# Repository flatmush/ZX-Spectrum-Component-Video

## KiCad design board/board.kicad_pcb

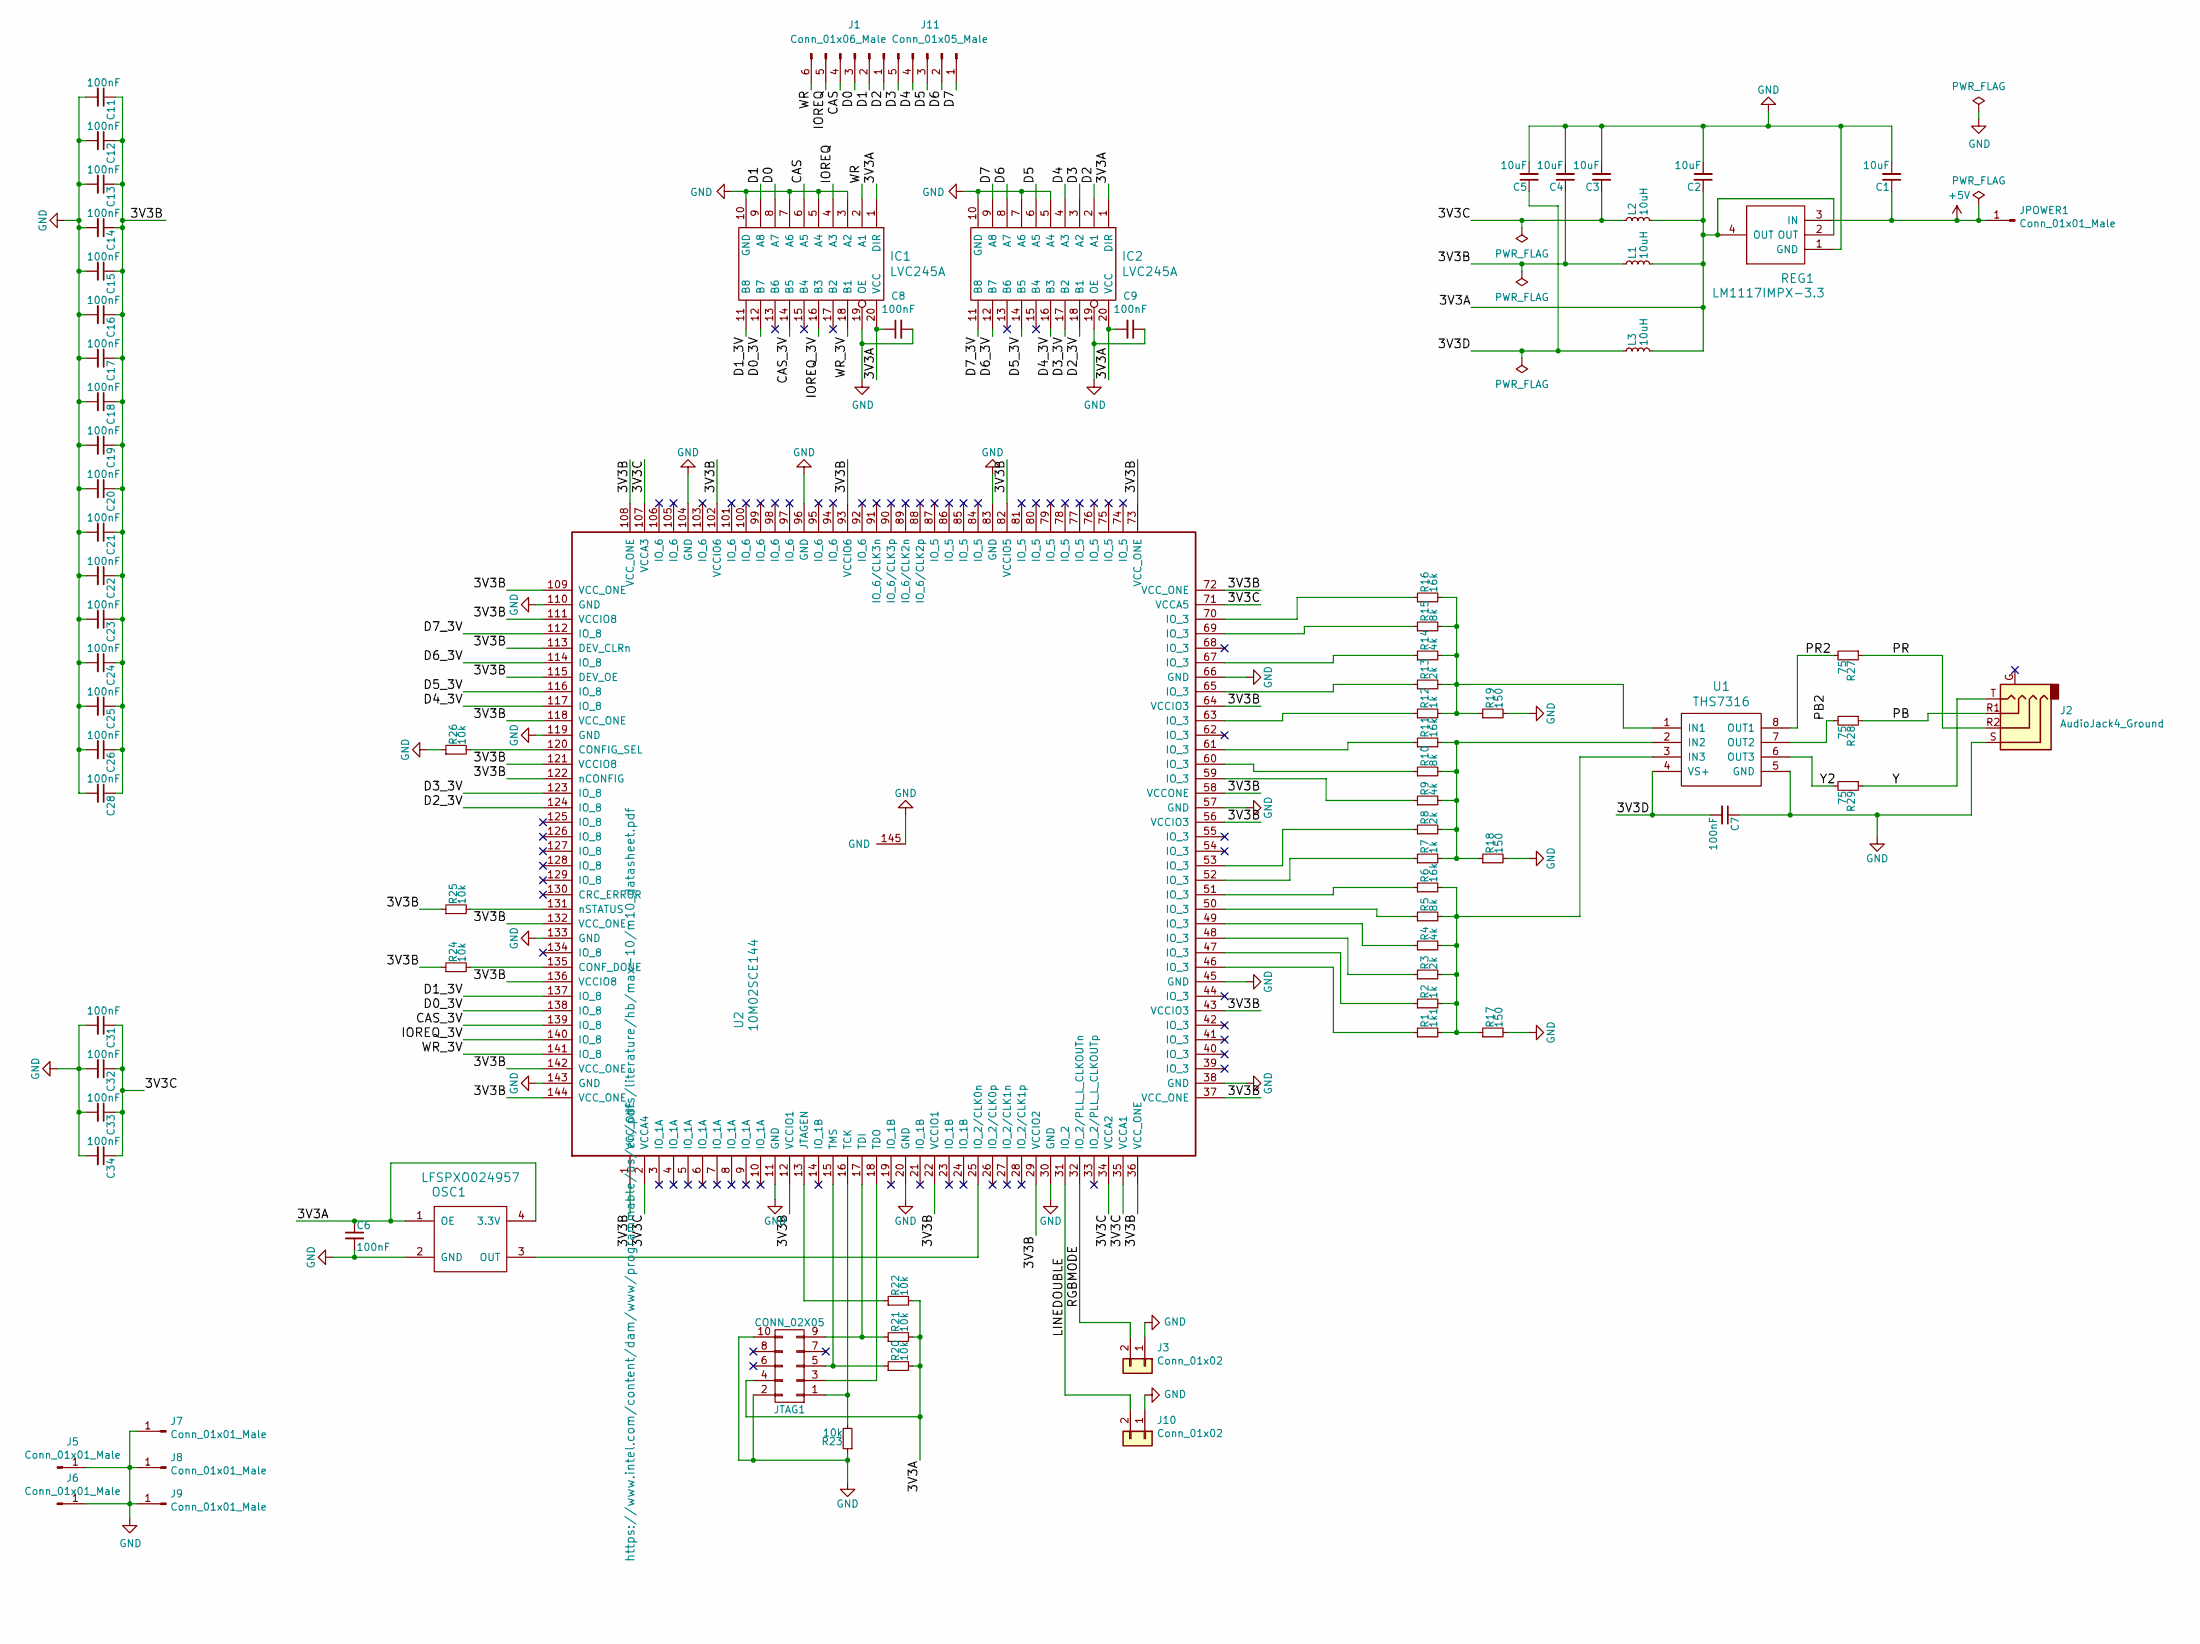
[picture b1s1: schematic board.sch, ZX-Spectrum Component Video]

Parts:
C1, C2, C3, C4, C5: 10uF; C_0805_2012Metric
C6, C7, C8, C9, C11, C12, C13, C14, C15, C16, C17, C18, C19, C20, C21, C22, C23, C24, C25, C26, C28, C31, C32, C33, C34: 100nF; C_0402_1005Metric
IC1, IC2: LVC245A; SSOP-20_5.3x7.2mm_P0.65mm
J1: Conn_01x06_Male; PinHeader_1x06_P2.54mm_Vertical
J2: AudioJack4_Ground; Conrad 4pin audio jack
J3, J10: Conn_01x02; PinHeader_2x01_P2.54mm_Vertical
J5, J6, J7, J8, J9: Conn_01x01_Male; PinHeader_1x01_P2.54mm_Vertical
J11: Conn_01x05_Male; PinHeader_1x05_P2.54mm_Vertical
JPOWER1: Conn_01x01_Male; PinHeader_1x01_P2.54mm_Vertical
JTAG1: CONN_02X05; PinHeader_2x05_P2.54mm_Vertical
L1, L2, L3: 10uH; L_0805_2012Metric_Pad1.15x1.40mm_HandSolder
OSC1: LFSPXO024957; Oscillator_SMD_EuroQuartz_XO53-4Pin_5.0x3.2mm_HandSoldering
R1: 1k1; R_0603_1608Metric
R2, R7, R12: 1k; R_0402_1005Metric
R3, R8, R13: 2k; R_0402_1005Metric
R4, R9, R14: 4k; R_0402_1005Metric
R5, R10, R15: 8k; R_0402_1005Metric
R6, R11, R16: 16k; R_0402_1005Metric
R17, R18, R19: 150; R_0402_1005Metric
R20, R21, R22, R23, R24, R25, R26: 10k; R_0402_1005Metric
R27, R28, R29: 75; R_0402_1005Metric
REG1: LM1117IMPX-3.3; SOT-223
U1: THS7316; SOIC-8_3.9x4.9mm_P1.27mm
U2: 10M02SCE144; QFP_144_GND

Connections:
+5V: C1.1, JPOWER1.1, REG1.3 (IN)
/3V3A: C2.1, C6.1, C8.1, C9.2, IC1.1 (DIR), IC1.20 (VCC), IC2.1 (DIR), IC2.20 (VCC), JTAG1.4, L1.2, L2.2, L3.2, OSC1.1 (OE), OSC1.4 (3.3V), R20.2, R21.2, R22.2, REG1.2 (OUT), REG1.4 (OUT)
/3V3B: C4.1, C11.1, C12.1, C13.1, C14.1, C15.1, C16.1, C17.1, C18.1, C19.1, C20.1, C21.1, C22.1, C23.1, C24.1, C25.1, C26.1, C28.1, L1.1, R24.1, R25.1, U2.1 (VCC_ONE), U2.12 (VCCIO1), U2.22 (VCCIO1), U2.29 (VCCIO2), U2.36 (VCC_ONE), U2.37 (VCC_ONE), U2.43 (VCCIO3), U2.56 (VCCIO3), U2.58 (VCCONE), U2.64 (VCCIO3), U2.72 (VCC_ONE), U2.73 (VCC_ONE), U2.82 (VCCIO5), U2.93 (VCCIO6), U2.102 (VCCIO6), U2.108 (VCC_ONE), U2.109 (VCC_ONE), U2.111 (VCCIO8), U2.113 (DEV_CLRn), U2.115 (DEV_OE), U2.118 (VCC_ONE), U2.121 (VCCIO8), U2.122 (nCONFIG), U2.132 (VCC_ONE), U2.136 (VCCIO8), U2.142 (VCC_ONE), U2.144 (VCC_ONE)
/3V3C: C3.1, C31.1, C32.1, C33.1, C34.1, L2.1, U2.2 (VCCA4), U2.34 (VCCA2), U2.35 (VCCA1), U2.71 (VCCA5), U2.107 (VCCA3)
/3V3D: C5.1, C7.2, L3.1, U1.4 (VS+)
/CAS: IC1.6 (A5), J1.4
/CAS_3V: IC1.14 (B5), U2.139 (IO_8)
/D0: IC1.8 (A7), J1.3
/D0_3V: IC1.12 (B7), U2.138 (IO_8)
/D1: IC1.9 (A8), J1.2
/D1_3V: IC1.11 (B8), U2.137 (IO_8)
/D2: IC2.2 (A1), J1.1
/D2_3V: IC2.18 (B1), U2.124 (IO_8)
/D3: IC2.3 (A2), J11.5
/D3_3V: IC2.17 (B2), U2.123 (IO_8)
/D4: IC2.4 (A3), J11.4
/D4_3V: IC2.16 (B3), U2.117 (IO_8)
/D5: IC2.6 (A5), J11.3
/D5_3V: IC2.14 (B5), U2.116 (IO_8)
/D6: IC2.8 (A7), J11.2
/D6_3V: IC2.12 (B7), U2.114 (IO_8)
/D7: IC2.9 (A8), J11.1
/D7_3V: IC2.11 (B8), U2.112 (IO_8)
/IOREQ: IC1.4 (A3), J1.5
/IOREQ_3V: IC1.16 (B3), U2.140 (IO_8)
/LINEDOUBLE: J10.2, U2.31 (IO_2)
/PB: J2.R1, R28.1
/PB2: R28.2, U1.7 (OUT2)
/PR: J2.R2, R27.1
/PR2: R27.2, U1.8 (OUT1)
/RGBMODE: J3.2, U2.32 (IO_2/PLL_L_CLKOUTn)
/WR: IC1.2 (A1), J1.6
/WR_3V: IC1.18 (B1), U2.141 (IO_8)
/Y: J2.T, R29.1
/Y2: R29.2, U1.6 (OUT3)
GND: C1.2, C2.2, C3.2, C4.2, C5.2, C6.2, C7.1, C8.2, C9.1, C11.2, C12.2, C13.2, C14.2, C15.2, C16.2, C17.2, C18.2, C19.2, C20.2, C21.2, C22.2, C23.2, C24.2, C25.2, C26.2, C28.2, C31.2, C32.2, C33.2, C34.2, IC1.3 (A2), IC1.5 (A4), IC1.7 (A6), IC1.10 (GND), IC1.19 (OE), IC2.5 (A4), IC2.7 (A6), IC2.10 (GND), IC2.19 (OE), J2.S, J3.1, J5.1, J6.1, J7.1, J8.1, J9.1, J10.1, JTAG1.2, JTAG1.10, OSC1.2 (GND), R17.2, R18.2, R19.2, R23.1, R26.1, REG1.1 (GND), U1.5 (GND), U2.11 (GND), U2.20 (GND), U2.30 (GND), U2.38 (GND), U2.45 (GND), U2.57 (GND), U2.66 (GND), U2.83 (GND), U2.96 (GND), U2.104 (GND), U2.110 (GND), U2.119 (GND), U2.133 (GND), U2.143 (GND), U2.145 (GND)
unnamed: JTAG1.1, R23.2, U2.16 (TCK)
unnamed: JTAG1.3, U2.18 (TDO)
unnamed: JTAG1.5, R20.1, U2.15 (TMS)
unnamed: JTAG1.9, R21.1, U2.17 (TDI)
unnamed: OSC1.3 (OUT), U2.25 (IO_2/CLK0n)
unnamed: R1.1, U2.46 (IO_3)
unnamed: R1.2, R2.2, R3.2, R4.2, R5.2, R6.2, R17.1, U1.3 (IN3)
unnamed: R2.1, U2.47 (IO_3)
unnamed: R3.1, U2.48 (IO_3)
unnamed: R4.1, U2.49 (IO_3)
unnamed: R5.1, U2.50 (IO_3)
unnamed: R6.1, U2.51 (IO_3)
unnamed: R7.1, U2.52 (IO_3)
unnamed: R8.1, U2.53 (IO_3)
unnamed: R9.1, U2.59 (IO_3)
unnamed: R10.1, U2.60 (IO_3)
unnamed: R7.2, R8.2, R9.2, R10.2, R11.2, R18.1, U1.2 (IN2)
unnamed: R11.1, U2.61 (IO_3)
unnamed: R12.1, U2.63 (IO_3)
unnamed: R12.2, R13.2, R14.2, R15.2, R16.2, R19.1, U1.1 (IN1)
unnamed: R13.1, U2.65 (IO_3)
unnamed: R14.1, U2.67 (IO_3)
unnamed: R15.1, U2.69 (IO_3)
unnamed: R16.1, U2.70 (IO_3)
unnamed: R22.1, U2.13 (JTAGEN)
unnamed: R24.2, U2.135 (CONF_DONE)
unnamed: R25.2, U2.131 (nSTATUS)
unnamed: R26.2, U2.120 (CONFIG_SEL)

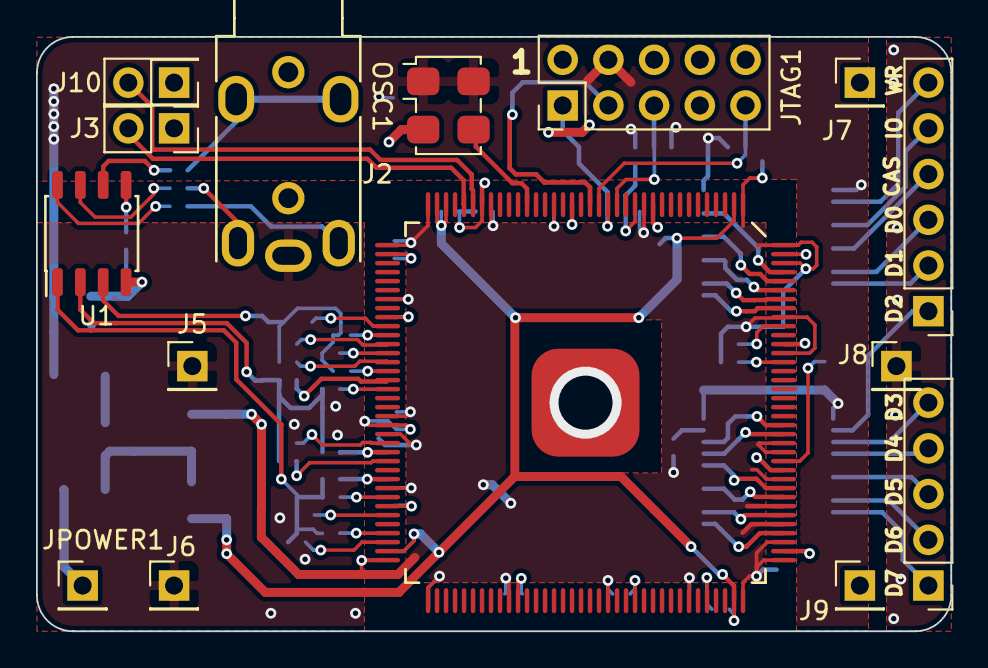
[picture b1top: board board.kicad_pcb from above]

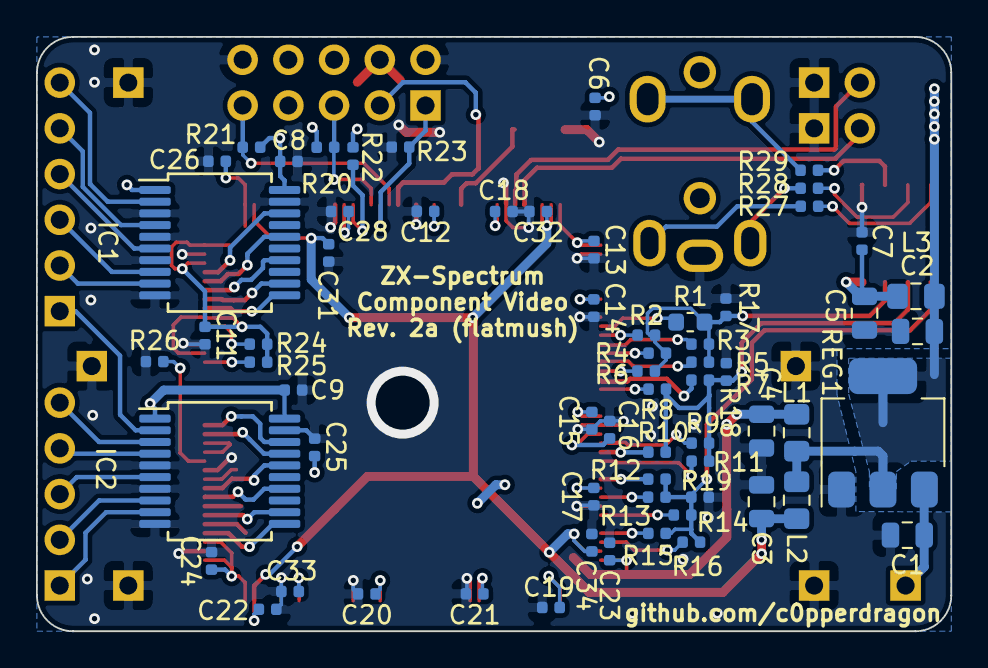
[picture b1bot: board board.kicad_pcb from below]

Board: 2 copper layers, 50.8 x 33.0 mm, 80 parts (65 on the bottom side), 64 nets.

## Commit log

2021-03-26 Rework to be manufacturable by JLCPCB
